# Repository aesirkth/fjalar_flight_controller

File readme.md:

# Fjalar flight controller
Fjalar is a rooster in Jotunheim who heralds the advent of ragnarök, or in our case, apogee.

### features
1. 3 pyro channels
1. barometer
1. IMU
1. GPS
1. USB-C
1. flash memory
1. CAN, I2C, UART connectors
1. LoRa radio
1. continuity detection

### schematic
see [here](./design/euroc_controller.pdf)

### hardware
hopefully soon :)

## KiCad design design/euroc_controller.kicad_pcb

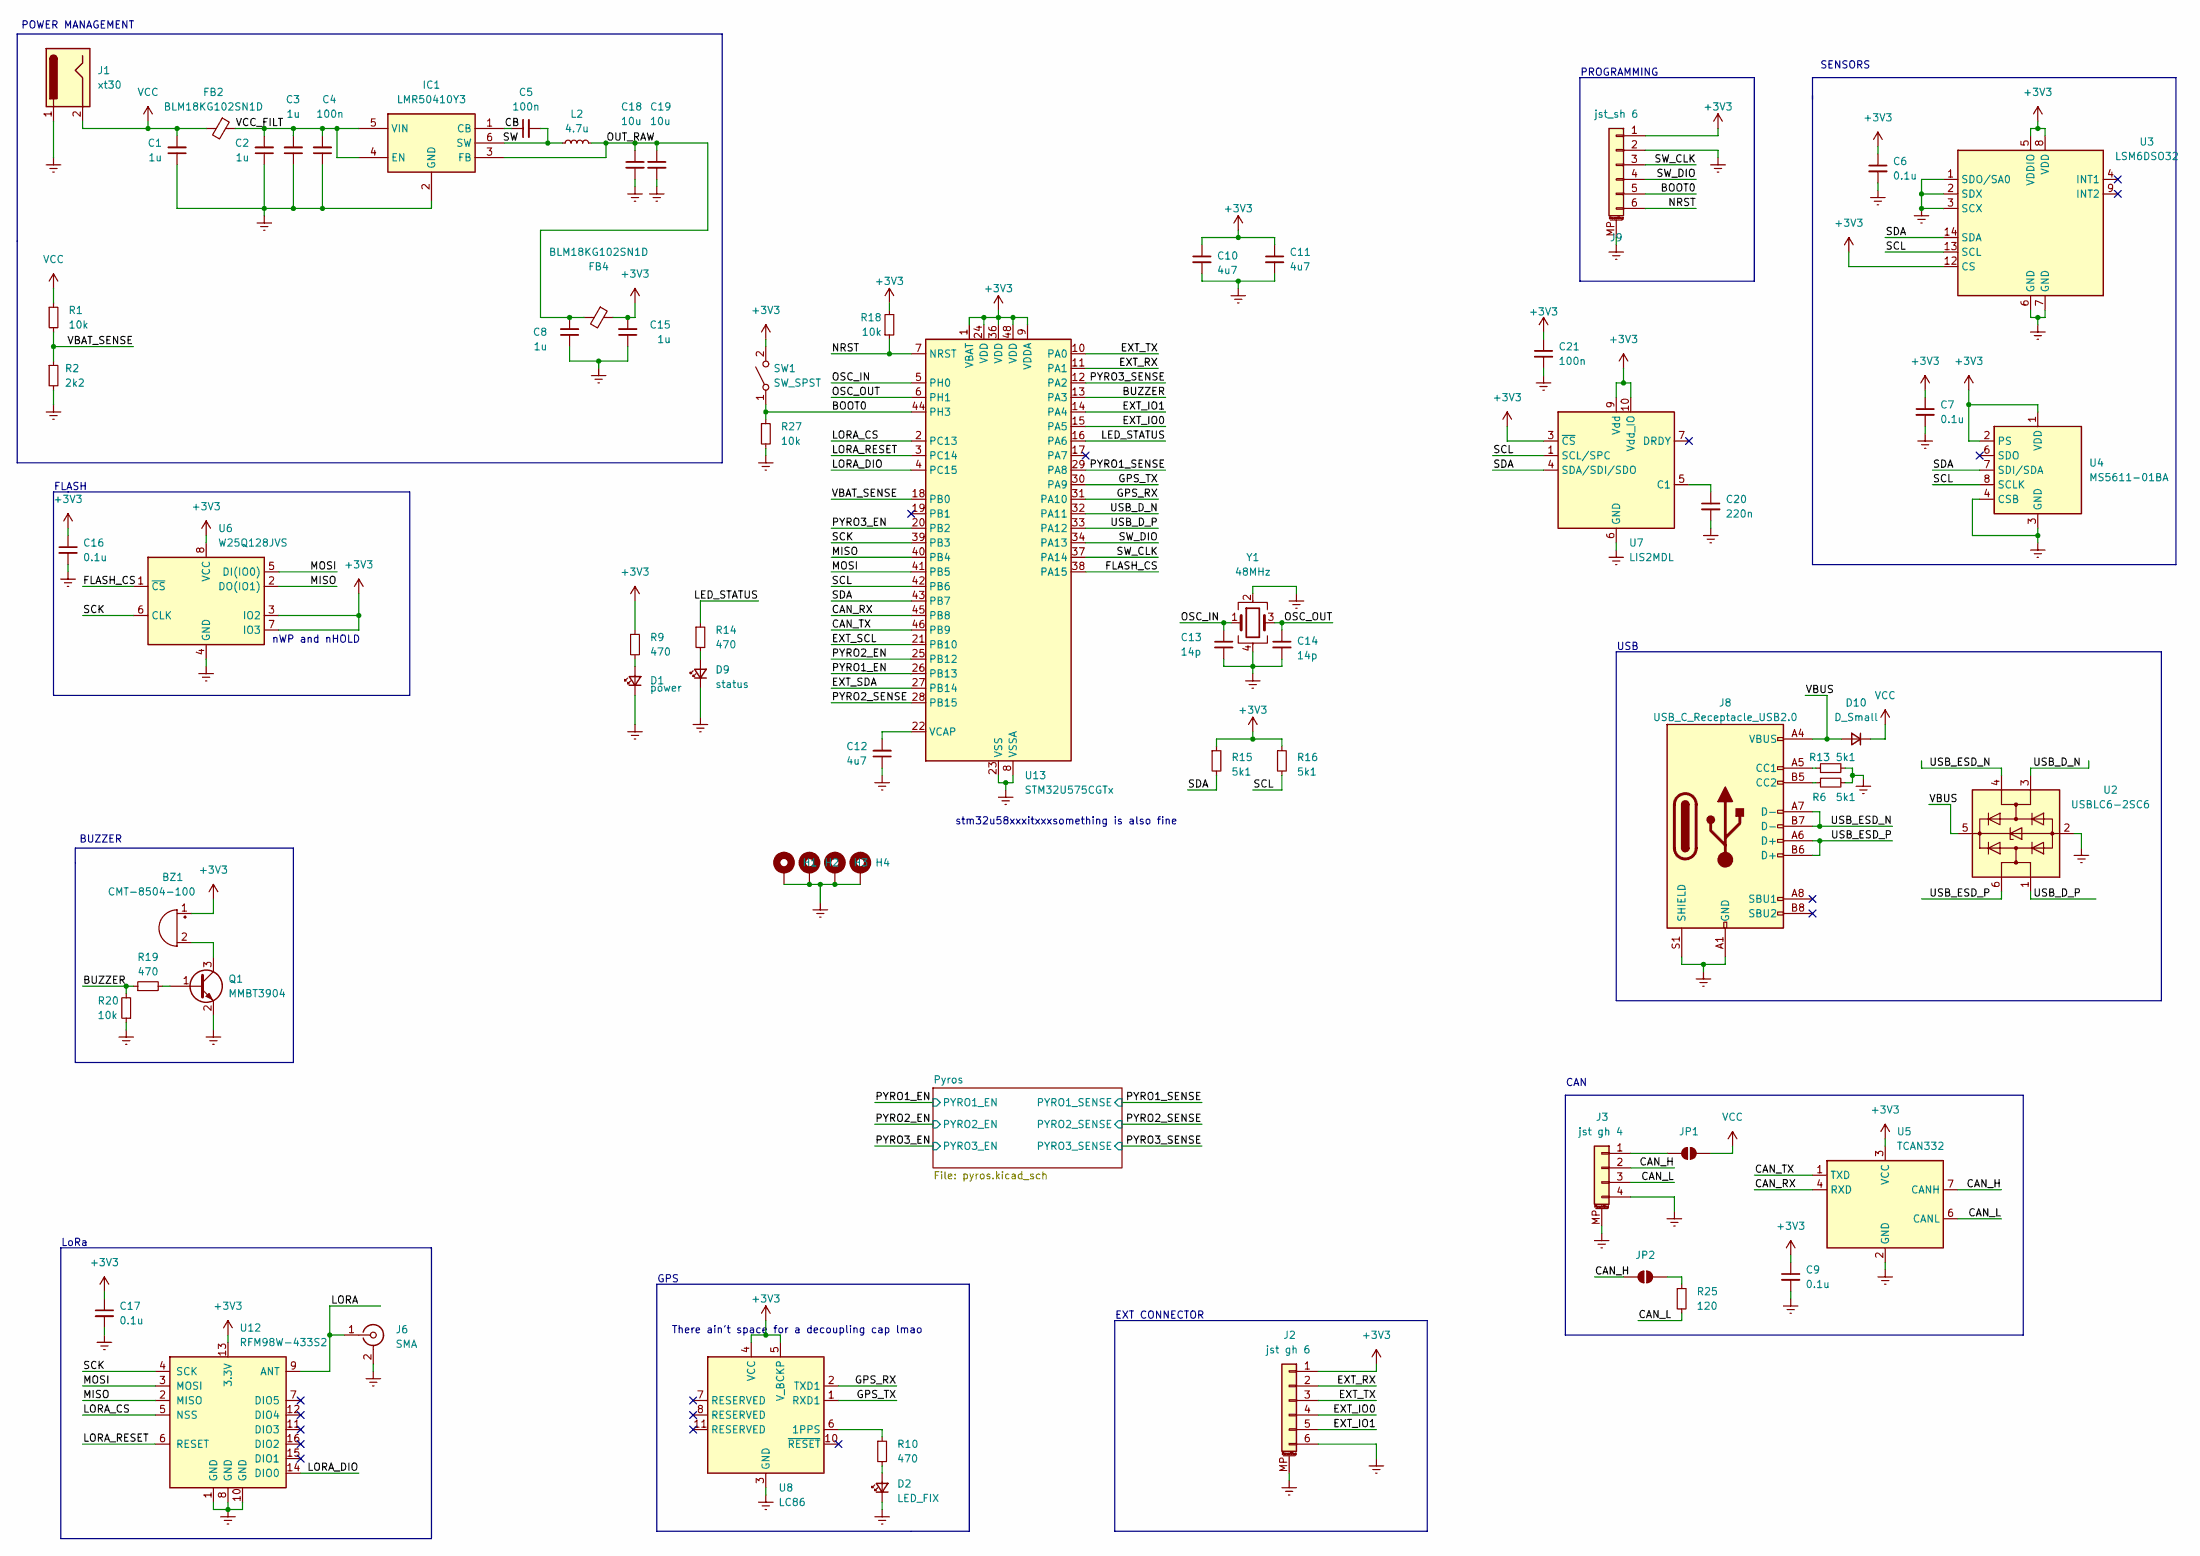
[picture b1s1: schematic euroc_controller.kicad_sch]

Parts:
BZ1: CMT-8504-100; MagneticBuzzer_CUI_CMT-8504-100-SMT
C1, C2, C3, C8, C15: 1u; C_0603_1608Metric
C4, C5, C21: 100n; C_0603_1608Metric
C6, C7, C9, C16, C17: 0.1u; C_0603_1608Metric
C10, C11, C12: 4u7; C_0603_1608Metric
C13, C14: 14p; C_0603_1608Metric
C18, C19: 10u; C_0603_1608Metric
C20: 220n; C_0603_1608Metric
D1: power; D_0603_1608Metric
D2: LED_FIX; D_0603_1608Metric
D9: status; D_0603_1608Metric
D10: D_Small; D_SOD-323_HandSoldering
FB2, FB4: BLM18KG102SN1D; L_0805_2012Metric_Pad1.15x1.40mm_HandSolder
H1, H2, H3, H4: MountingHole_Pad; MountingHole_2.2mm_M2_Pad_Via
IC1: LMR50410Y3; SOT-23-6_Handsoldering; Mouser Part Number 595-LMR50410YQDBVRQ1
J1: xt30; AMASS_XT30PW-M_1x02_P2.50mm_Horizontal
J2: jst gh 6; JST_GH_SM06B-GHS-TB_1x06-1MP_P1.25mm_Horizontal
J3: jst gh 4; JST_GH_SM04B-GHS-TB_1x04-1MP_P1.25mm_Horizontal
J6: SMA; SMA_Amphenol_901-143_Horizontal
J8: USB_C_Receptacle_USB2.0; USB_C_Receptacle_Palconn_UTC16-G
J9: jst_sh 6; JST_SH_SM06B-SRSS-TB_1x06-1MP_P1.00mm_Horizontal
JP1, JP2: SolderJumper_2_Open; SolderJumper-2_P1.3mm_Open_TrianglePad1.0x1.5mm
L2: 4.7u; L_Wurth_WE-LQSH-3012
Q1: MMBT3904; SOT-23
R1, R18, R20, R27: 10k; R_0603_1608Metric
R2: 2k2; R_0603_1608Metric
R6, R13, R15, R16: 5k1; R_0603_1608Metric
R9, R10, R14, R19: 470; R_0603_1608Metric
R25: 120; R_0603_1608Metric
SW1: SW_SPST; SW_SPST_B3U-1000P
U2: USBLC6-2SC6; SOT-23-6
U3: LSM6DSO32; LGA-14_3x2.5mm_P0.5mm_LayoutBorder3x4y
U4: MS5611-01BA; LGA-8_3x5mm_P1.25mm
U5: TCAN332; SOIC-8_3.9x4.9mm_P1.27mm
U6: W25Q128JVS; SOIC-8_5.23x5.23mm_P1.27mm
U7: LIS2MDL; LGA-12_2x2mm_P0.5mm
U8: LC86; Quectel_L80-R
U12: RFM98W-433S2; HOPERF_RFM9XW_SMD
U13: STM32U575CGTx; LQFP-48_7x7mm_P0.5mm
Y1: 48MHz; Crystal_SMD_2016-4Pin_2.0x1.6mm

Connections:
+3V3: BZ1.1 (-), C6.1, C7.1, C9.1, C10.1, C11.1, C15.2, C16.1, C17.1, C21.1, FB4.1, J2.1, J9.1, R9.1, R15.1, R16.1, R18.2, SW1.2 (B), U3.5 (VDDIO), U3.8 (VDD), U3.12 (CS), U4.1 (VDD), U4.2 (PS), U5.3 (VCC), U6.3 (IO2), U6.7 (IO3), U6.8 (VCC), U7.3 (~CS), U7.9 (Vdd), U7.10 (Vdd_IO), U8.4 (VCC), U8.5 (V_BCKP), U12.13 (3.3V), U13.1 (VBAT), U13.9 (VDDA), U13.24 (VDD), U13.36 (VDD), U13.48 (VDD)
/BOOT0: J9.5, R27.1, SW1.1 (A), U13.44 (PH3)
/BUZZER: R19.1, R20.2, U13.13 (PA3)
/CAN_H: J3.2, JP2.2 (B), U5.7 (CANH)
/CAN_L: J3.3, R25.2, U5.6 (CANL)
/CAN_RX: U5.4 (RXD), U13.45 (PB8)
/CAN_TX: U5.1 (TXD), U13.46 (PB9)
/CB: C5.1, IC1.1 (CB)
/EXT_IO0: J2.4, U13.15 (PA5)
/EXT_IO1: J2.5, U13.14 (PA4)
/EXT_RX: J2.2, U13.11 (PA1)
/EXT_SCL: U13.21 (PB10)
/EXT_SDA: U13.27 (PB14)
/EXT_TX: J2.3, U13.10 (PA0)
/FLASH_CS: U6.1 (~CS), U13.38 (PA15)
/GPS_RX: U8.2 (TXD1), U13.31 (PA10)
/GPS_TX: U8.1 (RXD1), U13.30 (PA9)
/LED_STATUS: R14.1, U13.16 (PA6)
/LORA: J6.1 (In), U12.9 (ANT)
/LORA_CS: U12.5 (NSS), U13.2 (PC13)
/LORA_DIO: U12.14 (DIO0), U13.4 (PC15)
/LORA_RESET: U12.6 (RESET), U13.3 (PC14)
/MISO: U6.2 (DO(IO1)), U12.2 (MISO), U13.40 (PB4)
/MOSI: U6.5 (DI(IO0)), U12.3 (MOSI), U13.41 (PB5)
/NRST: J9.6, R18.1, U13.7 (NRST)
/OSC_IN: C13.1, U13.5 (PH0), Y1.1
/OSC_OUT: C14.1, U13.6 (PH1), Y1.3
/OUT_RAW: C8.2, C18.1, C19.1, FB4.2, IC1.3 (FB), L2.2
/PYRO1_EN: U13.26 (PB13); also elsewhere on the board
/PYRO1_SENSE: U13.29 (PA8); also elsewhere on the board
/PYRO2_EN: U13.25 (PB12); also elsewhere on the board
/PYRO2_SENSE: U13.28 (PB15); also elsewhere on the board
/PYRO3_EN: U13.20 (PB2); also elsewhere on the board
/PYRO3_SENSE: U13.12 (PA2); also elsewhere on the board
/SCK: U6.6 (CLK), U12.4 (SCK), U13.39 (PB3)
/SCL: R16.2, U3.13 (SCL), U4.8 (SCLK), U7.1 (SCL/SPC), U13.42 (PB6)
/SDA: R15.2, U3.14 (SDA), U4.7 (SDI/SDA), U7.4 (SDA/SDI/SDO), U13.43 (PB7)
/SW: C5.2, IC1.6 (SW), L2.1
/SW_CLK: J9.3, U13.37 (PA14)
/SW_DIO: J9.4, U13.34 (PA13)
/USB_D_N: U2.3 (I/O2), U13.32 (PA11)
/USB_D_P: U2.1 (I/O1), U13.33 (PA12)
/USB_ESD_N: J8.A7 (D-), J8.B7 (D-), U2.4 (I/O2)
/USB_ESD_P: J8.A6 (D+), J8.B6 (D+), U2.6 (I/O1)
/VBAT_SENSE: R1.2, R2.1, U13.18 (PB0)
/VBUS: D10.2 (A), J8.A4 (VBUS), J8.A9 (VBUS), J8.B4 (VBUS), J8.B9 (VBUS), U2.5 (VBUS)
/VCC_FILT: C2.2, C3.2, C4.2, FB2.1, IC1.4 (EN), IC1.5 (VIN)
Earth: C1.1, C2.1, C3.1, C4.1, C6.2, C7.2, C8.1, C9.2, C10.2, C11.2, C12.1, C13.2, C14.2, C15.1, C16.2, C17.2, C18.2, C19.2, C20.2, C21.2, D1.1 (K), D2.1 (K), D9.1 (K), H1.1, H2.1, H3.1, H4.1, IC1.2 (GND), J1.1, J2.6, J2.MP (MountPin), J3.4, J3.MP (MountPin), J6.2 (Ext), J8.A1 (GND), J8.A12 (GND), J8.B1 (GND), J8.B12 (GND), J8.S1 (SHIELD), J9.2, J9.MP (MountPin), Q1.2 (E), R2.2, R6.2, R13.2, R20.1, R27.2, U2.2 (GND), U3.1 (SDO/SA0), U3.2 (SDX), U3.3 (SCX), U3.6 (GND), U3.7 (GND), U4.3 (GND), U4.4 (CSB), U4.5 (CSB), U5.2 (GND), U6.4 (GND), U7.6 (GND), U7.8 (GND), U8.3 (GND), U8.12 (GND), U12.1 (GND), U12.8 (GND), U12.10 (GND), U13.8 (VSSA), U13.23 (VSS), U13.35 (VSS), U13.47 (VSS), Y1.2, Y1.4; also elsewhere on the board
unnamed: BZ1.2 (+), Q1.3 (C)
unnamed: D1.2 (A), R9.2
unnamed: D2.2 (A), R10.2
unnamed: D9.2 (A), R14.2
unnamed: J3.1, JP1.2 (B)
unnamed: J8.A5 (CC1), R13.1
unnamed: J8.B5 (CC2), R6.1
unnamed: JP2.1 (A), R25.1
unnamed: Q1.1 (B), R19.2
unnamed: C20.1, U7.5 (C1)
unnamed: R10.1, U8.6 (1PPS)
unnamed: C12.2, U13.22 (VCAP)
VCC: C1.2, D10.1 (K), FB2.2, J1.2, JP1.1 (A), R1.1; also elsewhere on the board

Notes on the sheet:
GPS
POWER MANAGEMENT
nWP and nHOLD
USB
FLASH
BUZZER
There ain't space for a decoupling cap lmao
SENSORS
PROGRAMMING
LoRa
stm32u58xxxitxxxsomething is also fine
EXT CONNECTOR
CAN

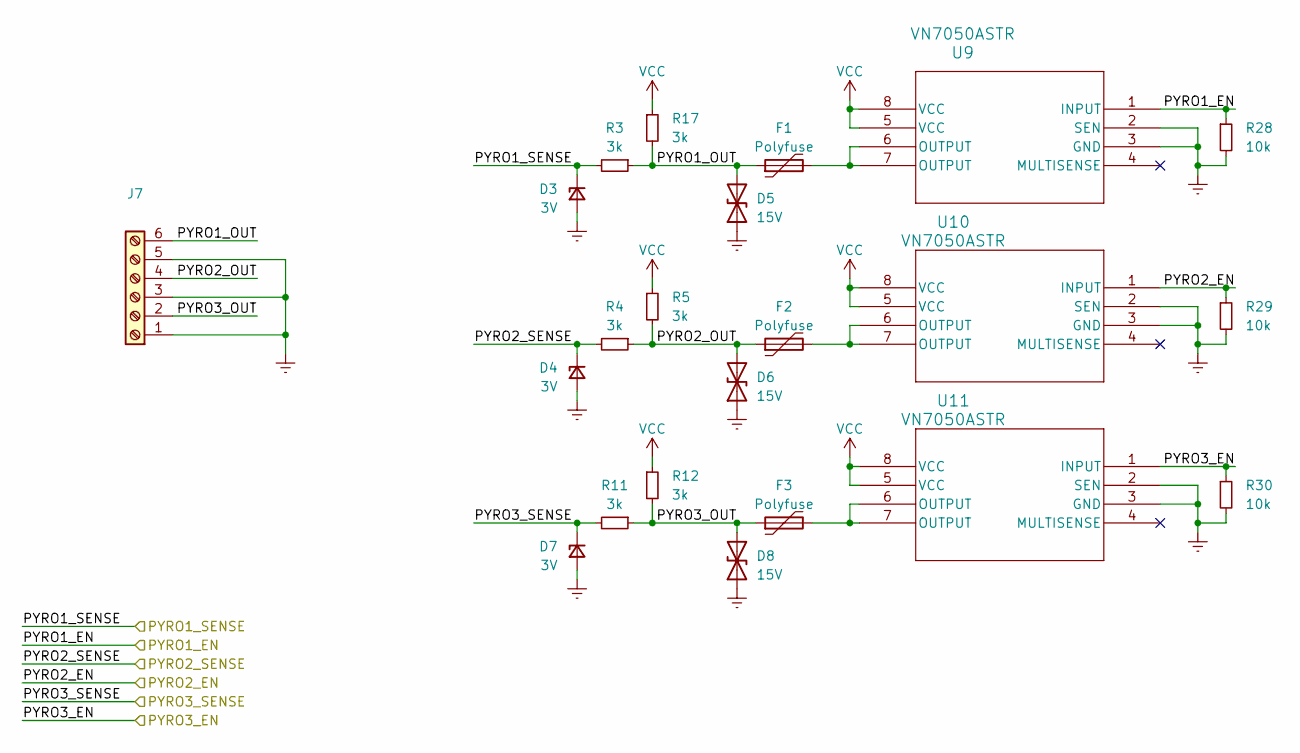
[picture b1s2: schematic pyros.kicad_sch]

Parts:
D3, D4, D7: 3V; D_SOD-323_HandSoldering
D5, D6, D8: 15V; D_0603_1608Metric
F1, F2, F3: Polyfuse; Fuse_1210_3225Metric_Pad1.42x2.65mm_HandSolder
J7: Screw_Terminal_01x06; TerminalBlock_TE_282834-6_1x06_P2.54mm_Horizontal
R3, R4, R5, R11, R12, R17: 3k; R_0603_1608Metric
R28, R29, R30: 10k; R_0603_1608Metric
U9, U10, U11: VN7050ASTR; SOIC_050ASTR_STM

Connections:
/PYRO1_EN: R28.1, U9.1 (INPUT); also elsewhere on the board
/PYRO1_SENSE: D3.1 (K), R3.2; also elsewhere on the board
/PYRO2_EN: R29.1, U10.1 (INPUT); also elsewhere on the board
/PYRO2_SENSE: D4.1 (K), R4.2; also elsewhere on the board
/PYRO3_EN: R30.1, U11.1 (INPUT); also elsewhere on the board
/PYRO3_SENSE: D7.1 (K), R11.2; also elsewhere on the board
/Pyros/PYRO1_OUT: D5.2 (A2), F1.1, J7.6, R3.1, R17.2
/Pyros/PYRO2_OUT: D6.2 (A2), F2.1, J7.4, R4.1, R5.2
/Pyros/PYRO3_OUT: D8.2 (A2), F3.1, J7.2, R11.1, R12.2
Earth: D3.2 (A), D4.2 (A), D5.1 (A1), D6.1 (A1), D7.2 (A), D8.1 (A1), J7.1, J7.3, J7.5, R28.2, R29.2, R30.2, U9.2 (SEN), U9.3 (GND), U10.2 (SEN), U10.3 (GND), U11.2 (SEN), U11.3 (GND); also elsewhere on the board
unnamed: F1.2, U9.6 (OUTPUT), U9.7 (OUTPUT)
unnamed: F2.2, U10.6 (OUTPUT), U10.7 (OUTPUT)
unnamed: F3.2, U11.6 (OUTPUT), U11.7 (OUTPUT)
VCC: R5.1, R12.1, R17.1, U9.5 (VCC), U9.8 (VCC), U10.5 (VCC), U10.8 (VCC), U11.5 (VCC), U11.8 (VCC); also elsewhere on the board

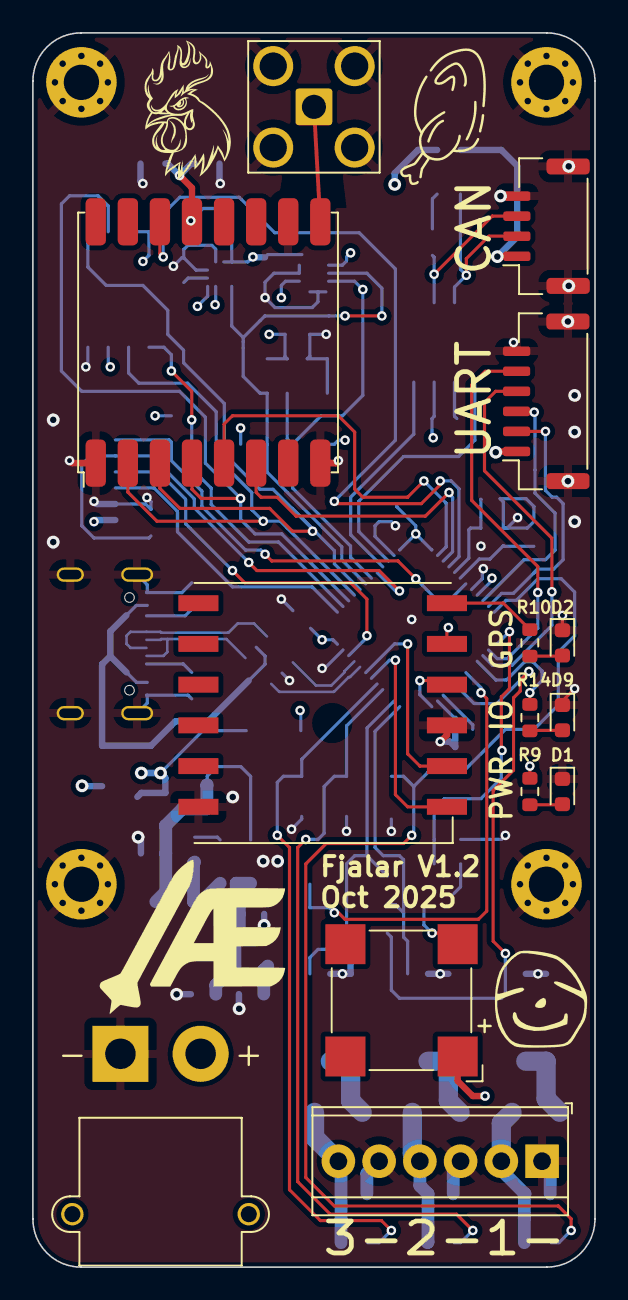
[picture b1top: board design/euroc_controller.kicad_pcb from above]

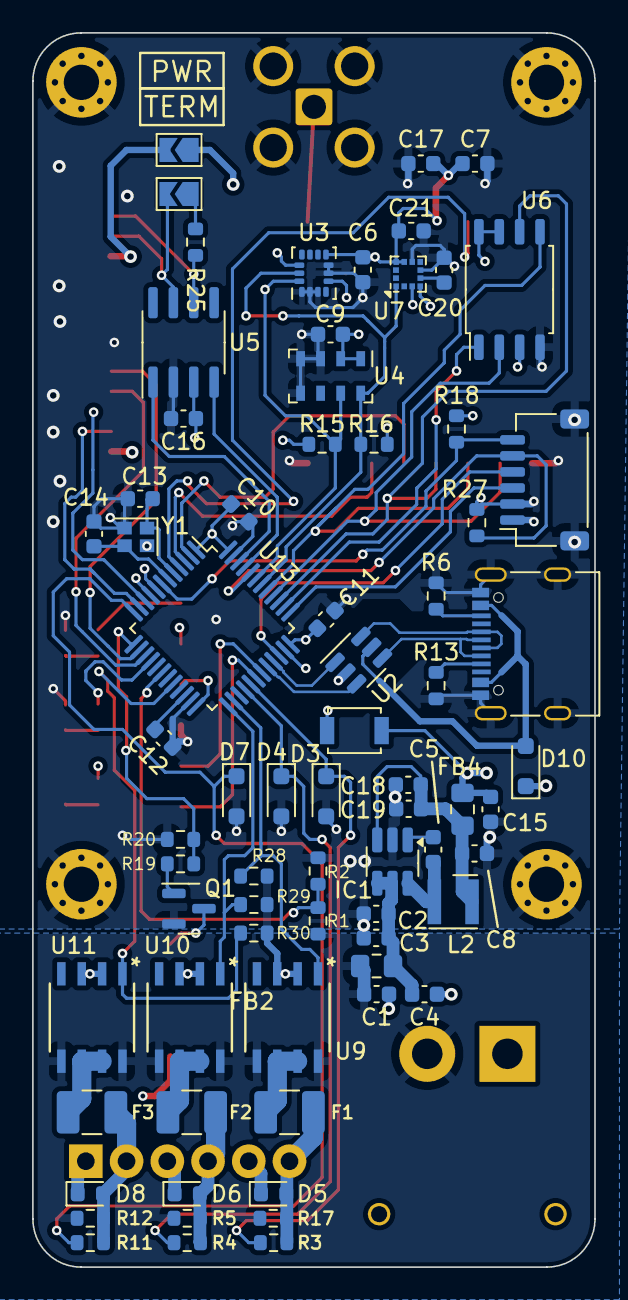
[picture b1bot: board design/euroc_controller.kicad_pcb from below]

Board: 4 copper layers, 35.1 x 77.0 mm, 90 parts (72 on the bottom side), 65 nets.

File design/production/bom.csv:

Designator,Footprint,Quantity,Value,LCSC Part #
BZ1,MagneticBuzzer_CUI_CMT-8504-100-SMT,1,CMT-8504-100,
"C1, C15, C2, C3, C8",0603,5,1u,
"C10, C11, C12",0603,3,4u7,
"C13, C14",0603,2,14p,
"C16, C17, C6, C7, C9",0603,5,0.1u,
"C18, C19",0603,2,10u,
C20,0603,1,220n,
"C21, C4, C5",0603,3,100n,
D1,0603,1,power,
D10,D_SOD-323_HandSoldering,1,D_Small,
D2,0603,1,LED_FIX,
"D3, D4, D7",D_SOD-323_HandSoldering,3,3V,
"D5, D6, D8",0603,3,15V,
D9,0603,1,status,
"F1, F2, F3",1210,3,Polyfuse,
"FB2, FB4",0805,2,BLM18KG102SN1D,
"H1, H2, H3, H4",MountingHole_2.2mm_M2_Pad_Via,4,MountingHole_Pad,
IC1,SOT-23-6_Handsoldering,1,LMR50410Y3,
J1,AMASS_XT30PW-M_1x02_P2.50mm_Horizontal,1,xt30,
J2,JST_GH_SM06B-GHS-TB_1x06-1MP_P1.25mm_Horizontal,1,jst gh 6,
J3,JST_GH_SM04B-GHS-TB_1x04-1MP_P1.25mm_Horizontal,1,jst gh 4,
J6,SMA_Amphenol_901-143_Horizontal,1,SMA,
J7,TerminalBlock_TE_282834-6_1x06_P2.54mm_Horizontal,1,Screw_Terminal_01x06,
J8,USB_C_Receptacle_Palconn_UTC16-G,1,USB_C_Receptacle_USB2.0,
J9,JST_SH_SM06B-SRSS-TB_1x06-1MP_P1.00mm_Horizontal,1,jst_sh 6,
L2,L_Wurth_WE-LQSH-3012,1,4.7u,
Q1,SOT-23,1,MMBT3904,
"R1, R18, R20, R27, R28, R29, R30",0603,7,10k,
"R10, R14, R19, R9",0603,4,470,
"R11, R12, R17, R3, R4, R5",0603,6,3k,
"R13, R15, R16, R6",0603,4,5k1,
R2,0603,1,2k2,
R25,0603,1,120,
SW1,SW_SPST_B3U-1000P,1,SW_SPST,
"U10, U11, U9",SOIC_050ASTR_STM,3,VN7050ASTR,
U12,HOPERF_RFM9XW_SMD,1,RFM98W-433S2,
U13,LQFP-48_7x7mm_P0.5mm,1,STM32U575CGTx,
U2,SOT-23-6,1,USBLC6-2SC6,
U3,LGA-14_3x2.5mm_P0.5mm_LayoutBorder3x4y,1,LSM6DSO32,
U4,LGA-8_3x5mm_P1.25mm,1,MS5611-01BA,
U5,SOIC-8_3.9x4.9mm_P1.27mm,1,TCAN332,
U6,SOIC-8_5.23x5.23mm_P1.27mm,1,W25Q128JVS,
U7,LGA-12_2x2mm_P0.5mm,1,LIS2MDL,
U8,Quectel_L80-R,1,LC86,
Y1,Crystal_SMD_2016-4Pin_2.0x1.6mm,1,48MHz,

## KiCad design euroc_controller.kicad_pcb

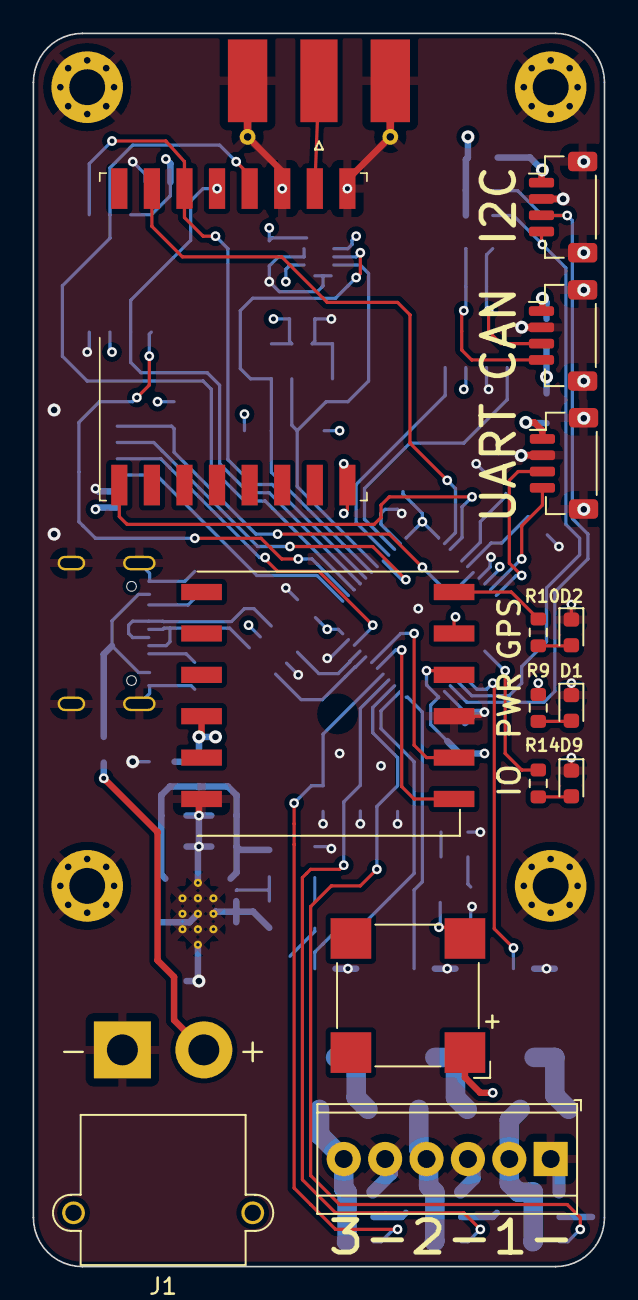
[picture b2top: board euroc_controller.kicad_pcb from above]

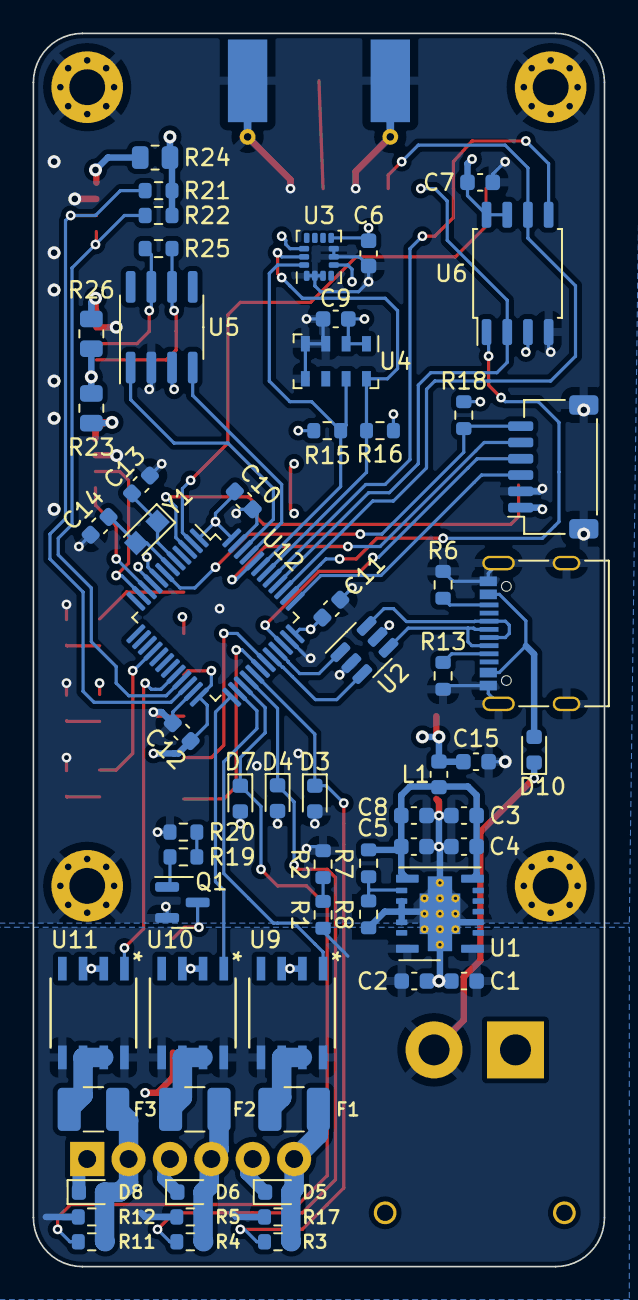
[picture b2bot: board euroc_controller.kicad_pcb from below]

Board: 4 copper layers, 35.1 x 75.7 mm, 82 parts (63 on the bottom side), 61 nets.

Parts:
BZ1: CMT-8504-100; MagneticBuzzer_CUI_CMT-8504-100-SMT
C1, C2, C10, C11: 4u7; C_0603_1608Metric
C3, C4, C5, C8, C15: 47u; C_0603_1608Metric
C6, C7, C9: 0.1u; C_0603_1608Metric
C12: 100p; C_0603_1608Metric
C13, C14: 22p; C_0603_1608Metric
D1: power; D_0603_1608Metric
D2: LED_FIX; D_0603_1608Metric
D3, D4, D7: 3V; D_0603_1608Metric
D5, D6, D8: 15V; D_0603_1608Metric
D9: status; D_0603_1608Metric
D10: D_Small; D_0603_1608Metric
F1, F2, F3: Polyfuse; Fuse_1210_3225Metric_Pad1.42x2.65mm_HandSolder
H1, H2, H3, H4: MountingHole_Pad; MountingHole_2.2mm_M2_Pad_Via
J1: xt30; AMASS_XT30PW-M_1x02_P2.50mm_Horizontal
J2, J4, J5: jst_sh 4; JST_SH_BM04B-SRSS-TB_1x04-1MP_P1.00mm_Vertical
J6: SMA; SMA_Molex_73251-1153_EdgeMount_Horizontal
J7: Screw_Terminal_01x06; TerminalBlock_TE_282834-6_1x06_P2.54mm_Horizontal
J8: USB_C_Receptacle_USB2.0; USB_C_Receptacle_Palconn_UTC16-G
J9: jst_sh 4; JST_SH_SM06B-SRSS-TB_1x06-1MP_P1.00mm_Horizontal
L1: L_Small; L_0603_1608Metric
Q1: MMBT3904; SOT-23
R1, R7, R18, R20: 10k; R_0603_1608Metric
R2: 2k2; R_0603_1608Metric
R3, R4, R5, R11, R12, R17: 47k; R_0603_1608Metric
R6, R13, R15, R16, R21, R22: 5k1; R_0603_1608Metric
R8: 4.3k; R_0603_1608Metric
R9, R10, R14, R19: 1k; R_0603_1608Metric
R23, R24, R26: 100; R_0805_2012Metric
R25: 120; R_0603_1608Metric
U1: TPSM5601R5; Texas_B3QFN-14-1EP_5x5.5mm_P0.65mm_ThermalVia
U2: USBLC6-2SC6; SOT-23-6
U3: LSM6DSO32; LGA-14_3x2.5mm_P0.5mm_LayoutBorder3x4y
U4: MS5611-01BA; LGA-8_3x5mm_P1.25mm
U5: SN65HVD232; SOIC-8_3.9x4.9mm_P1.27mm
U6: W25Q128JVS; SOIC-8_5.23x5.23mm_P1.27mm
U7: RFM69W; HOPERF_RFM69HW
U8: L86; Quectel_L80-R
U9, U10, U11: VN7050ASTR; SOIC_050ASTR_STM
U12: STM32L562CETx; LQFP-48_7x7mm_P0.5mm
Y1: 48MHz; Crystal_SMD_2012-2Pin_2.0x1.2mm_HandSoldering

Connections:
+3V3: BZ1.1 (-), C6.1, C7.1, C9.1, C10.1, C11.1, C12.1, C15.1, J9.1, L1.2, R9.1, R15.1, R16.1, R18.2, R21.1, R22.1, R23.2, R24.2, R26.2, U2.5 (VBUS), U3.5 (VDDIO), U3.8 (VDD), U3.12 (CS), U4.1 (VDD), U4.2 (PS), U5.3 (VCC), U6.3 (IO2), U6.7 (IO3), U6.8 (VCC), U7.8 (3.3V), U8.4 (VCC), U8.5 (V_BCKP), U8.10 (~RESET), U12.1 (VBAT), U12.9 (VDDA), U12.24 (VDD), U12.36 (VDD), U12.48 (VDD)
/BOOT0: J9.5, U12.44 (PH3)
/BUZZER: R19.1, R20.2
/CAN_H: J4.3, R25.1, U5.7 (CANH)
/CAN_L: J4.4, R25.2, U5.6 (CANL)
/CAN_RX: U5.4 (R), U12.45 (PB8)
/CAN_TX: U5.1 (D), U12.46 (PB9)
/EXT_RX: J5.3, U12.11 (PA1)
/EXT_SCL: J2.4, R22.2, U12.21 (PB10)
/EXT_SDA: J2.3, R21.2, U12.22 (PB11)
/EXT_TX: J5.4, U12.10 (PA0)
/FLASH_CS: U6.1 (~CS), U12.38 (PA15)
/GPS_RX: U8.2 (TXD1), U12.31 (PA10)
/GPS_TX: U8.1 (RXD1), U12.30 (PA9)
/LED_STATUS: R14.1, U12.16 (PA6)
/LORA_CS: U7.15 (NSS), U12.2 (PC13)
/LORA_RESET: U7.1 (RESET), U12.3 (PC14)
/MISO: U6.2 (DO(IO1)), U7.13 (MISO), U12.40 (PB4)
/MOSI: U6.5 (DI(IO0)), U7.14 (MOSI), U12.41 (PB5)
/NRST: J9.6, R18.1, U12.7 (NRST)
/OSC_IN: C13.1, U12.5 (PH0), Y1.1
/OSC_OUT: C14.1, U12.6 (PH1), Y1.2
/PYRO1_EN: U9.1 (INPUT), U12.26 (PB13)
/PYRO1_SENSE: D3.1 (K), R3.2, U12.29 (PA8)
/PYRO2_EN: U10.1 (INPUT), U12.25 (PB12)
/PYRO2_SENSE: D4.1 (K), R4.2, U12.28 (PB15)
/PYRO3_EN: U11.1 (INPUT), U12.20 (PB2)
/PYRO3_SENSE: D7.1 (K), R11.2, U12.27 (PB14)
/Pyros/PYRO1_OUT: D5.2 (A2), F1.1, J7.6, R3.1, R17.2
/Pyros/PYRO2_OUT: D6.2 (A2), F2.1, J7.4, R4.1, R5.2
/Pyros/PYRO3_OUT: D8.2 (A2), F3.1, J7.2, R11.1, R12.2
/SCK: U6.6 (CLK), U7.12 (SCK), U12.39 (PB3)
/SCL: R16.2, U3.13 (SCL), U4.8 (SCLK), U12.42 (PB6)
/SDA: R15.2, U3.14 (SDA), U4.7 (SDI/SDA), U12.43 (PB7)
/SW_CLK: J9.3, U12.37 (PA14)
/SW_DIO: J9.4, U12.34 (PA13)
/USB_D_N: U2.3 (I/O2), U12.32 (PA11)
/USB_D_P: U2.1 (I/O1), U12.33 (PA12)
/USB_ESD_N: J8.A7 (D-), J8.B7 (D-), U2.4 (I/O2)
/USB_ESD_P: J8.A6 (D+), J8.B6 (D+), U2.6 (I/O1)
/VBAT_SENSE: R1.2, R2.1
Earth: C1.2, C2.2, C3.2, C4.2, C5.2, C6.2, C7.2, C8.2, C9.2, C10.2, C11.2, C12.2, C13.2, C14.2, C15.2, D1.1 (K), D2.1 (K), D3.2 (A), D4.2 (A), D5.1 (A1), D6.1 (A1), D7.2 (A), D8.1 (A1), D9.1 (K), H1.1, H2.1, H3.1, H4.1, J1.1, J2.2, J2.MP (MountPin), J4.2, J4.MP (MountPin), J5.2, J5.MP (MountPin), J6.2 (Ext), J7.1, J7.3, J7.5, J8.A1 (GND), J8.A12 (GND), J8.B1 (GND), J8.B12 (GND), J8.S1 (SHIELD), J9.2, J9.MP (MountPin), Q1.2 (E), R2.2, R6.2, R8.2, R13.2, R20.1, U1.3 (PGND), U1.10 (PGND), U1.11 (PGND), U1.12 (AGND), U1.15 (PGND), U2.2 (GND), U3.1 (SDO/SA0), U3.2 (SDX), U3.3 (SCX), U3.6 (GND), U3.7 (GND), U4.3 (GND), U4.4 (CSB), U4.5 (CSB), U5.2 (GND), U6.4 (GND), U7.9 (GND), U7.11 (GND), U8.3 (GND), U8.12 (GND), U9.2 (SEN), U9.3 (GND), U10.2 (SEN), U10.3 (GND), U11.2 (SEN), U11.3 (GND), U12.8 (VSSA), U12.23 (VSS), U12.35 (VSS), U12.47 (VSS)
unnamed: BZ1.2 (+), Q1.3 (C)
unnamed: C3.1, C4.1, C5.1, C8.1, L1.1, R7.1, U1.7 (VOUT), U1.8 (VOUT)
unnamed: D1.2 (A), R9.2
unnamed: D2.2 (A), R10.2
unnamed: D9.2 (A), R14.2
unnamed: D10.2 (A), J8.A4 (VBUS), J8.A9 (VBUS), J8.B4 (VBUS), J8.B9 (VBUS)
unnamed: F1.2, U9.6 (OUTPUT), U9.7 (OUTPUT)
unnamed: F2.2, U10.6 (OUTPUT), U10.7 (OUTPUT)
unnamed: F3.2, U11.6 (OUTPUT), U11.7 (OUTPUT)
unnamed: J2.1, R24.1
unnamed: J4.1, R26.1
unnamed: J5.1, R23.1
unnamed: J6.1 (In), U7.10 (ANA)
unnamed: J8.A5 (CC1), R13.1
unnamed: J8.B5 (CC2), R6.1
unnamed: Q1.1 (B), R19.2
unnamed: R7.2, R8.1, U1.9 (FB)
unnamed: R10.1, U8.6 (1PPS)
VCC: C1.1, C2.1, D10.1 (K), J1.2, R1.1, R5.1, R12.1, R17.1, U1.1 (VIN), U1.2 (EN), U1.14 (VIN), U9.5 (VCC), U9.8 (VCC), U10.5 (VCC), U10.8 (VCC), U11.5 (VCC), U11.8 (VCC)

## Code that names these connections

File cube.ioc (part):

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Mcu.Name=STM32L562CETx
Mcu.Package=LQFP48
Mcu.UserName=STM32L562CETx
PA0.Signal=UART4_TX
PA1.Signal=UART4_RX
PA10.GPIOParameters=GPIO_Label
PA10.GPIO_Label=GPS_RX
PA10.Mode=Asynchronous
PA10.Signal=USART1_RX
PA11.Mode=Device
PA11.Signal=USB_DM
PA12.Mode=Device
PA12.Signal=USB_DP
PA13\ (JTMS/SWDIO).Mode=Serial_Wire
PA13\ (JTMS/SWDIO).Signal=DEBUG_JTMS-SWDIO
PA14\ (JTCK/SWCLK).Mode=Serial_Wire
PA14\ (JTCK/SWCLK).Signal=DEBUG_JTCK-SWCLK
PA15\ (JTDI).GPIOParameters=GPIO_Label
PA15\ (JTDI).GPIO_Label=FLASH_CS
PA15\ (JTDI).Signal=GPIO_Output
PA2.GPIOParameters=GPIO_Label
PA2.GPIO_Label=EXT_TX
PA2.Mode=Asynchronous
PA2.Signal=USART2_TX
PA3.GPIOParameters=GPIO_Label
PA3.GPIO_Label=EXT_RX
PA3.Mode=Asynchronous
PA3.Signal=USART2_RX
PA6.GPIOParameters=GPIO_Label
PA6.GPIO_Label=LED_STATUS
PA6.Signal=GPIO_Output
PA8.GPIOParameters=GPIO_Label
PA8.GPIO_Label=PYRO1_SENSE
PA8.Signal=GPIO_Input
PA9.GPIOParameters=GPIO_Label
PA9.GPIO_Label=GPS_TX
PA9.Mode=Asynchronous
PA9.Signal=USART1_TX
PB0.GPIOParameters=GPIO_Label
PB0.GPIO_Label=VBAT_SENSE
PB0.Signal=ADCx_IN15
PB10.Signal=I2C2_SCL
PB11.Signal=I2C2_SDA
PB12.GPIOParameters=GPIO_Label
PB12.GPIO_Label=PYRO2_EN
PB12.Signal=GPIO_Output
PB13.GPIOParameters=GPIO_Label
PB13.GPIO_Label=PYRO1_EN
PB13.Signal=GPIO_Output
PB14.GPIOParameters=GPIO_Label
PB14.GPIO_Label=PYRO3_SENSE
PB14.Signal=GPIO_Input
PB15.GPIOParameters=GPIO_Label
PB15.GPIO_Label=PYRO2_SENSE
PB15.Signal=GPIO_Input
PB2.GPIOParameters=GPIO_Label
PB2.GPIO_Label=PYRO3_EN
PB2.Signal=GPIO_Output
PB3\ (JTDO/TRACESWO).Mode=Full_Duplex_Master
PB3\ (JTDO/TRACESWO).Signal=SPI1_SCK
PB4\ (NJTRST).Mode=Full_Duplex_Master
PB4\ (NJTRST).Signal=SPI1_MISO
PB5.Mode=Full_Duplex_Master
PB5.Signal=SPI1_MOSI
PB6.Mode=I2C
PB6.Signal=I2C1_SCL
PB7.Mode=I2C
PB7.Signal=I2C1_SDA
PB8.Mode=FDCAN_Activate
PB8.Signal=FDCAN1_RX
PB9.Mode=FDCAN_Activate
PB9.Signal=FDCAN1_TX
PC13.GPIOParameters=GPIO_Label
PC13.GPIO_Label=LORA_CS
PC13.Signal=GPIO_Output
PC14-OSC32_IN\ (PC14).GPIOParameters=GPIO_Label
PC14-OSC32_IN\ (PC14).GPIO_Label=LORA_RESET
PC14-OSC32_IN\ (PC14).Signal=GPIO_Output
PH0-OSC_IN\ (PH0).Mode=HSE-External-Oscillator
PH0-OSC_IN\ (PH0).Signal=RCC_OSC_IN
PH1-OSC_OUT\ (PH1).Mode=HSE-External-Oscillator
PH1-OSC_OUT\ (PH1).Signal=RCC_OSC_OUT
RCC.HSE_VALUE=48000000
board=custom

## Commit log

2023-05-27 better structure
2023-05-27 bajs
2023-05-27 align mounting holes
2023-05-27 add basic readme
2023-05-27 fix markdown
2023-05-27 use real clock, fix esd vbus
2023-05-30 update ioc, add logo
2023-05-30 oof new umc (st32u5)
2023-05-30 fix new umc...
2023-05-30 can transceiver, decoupling caps
2023-05-31 fix aesir logo
2023-05-31 better sma
2023-06-15 route dp
2023-06-15 redo for aisler
2023-07-15 PCB 1.1 old regulator
2023-07-15 initial firmware
2023-08-02 virtual environment working
2023-08-02 PCB v1.1
2023-08-30 remove firmware
2024-03-13 Add pic
2025-10-26 v1.2
